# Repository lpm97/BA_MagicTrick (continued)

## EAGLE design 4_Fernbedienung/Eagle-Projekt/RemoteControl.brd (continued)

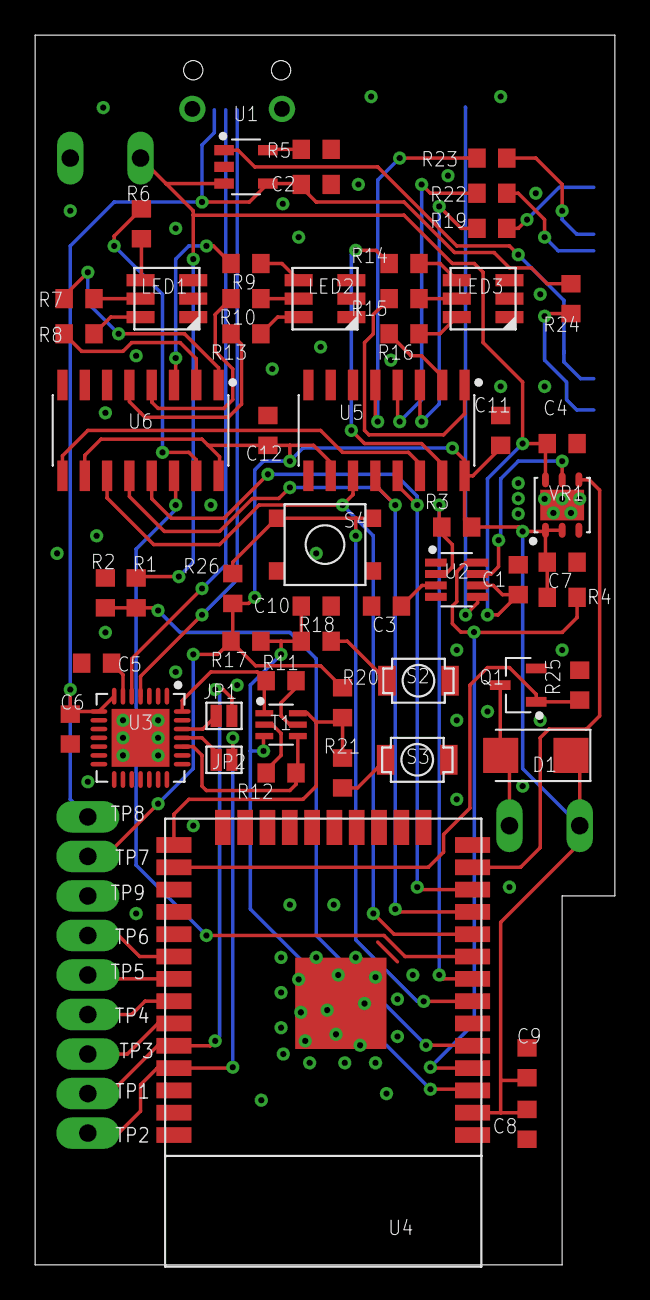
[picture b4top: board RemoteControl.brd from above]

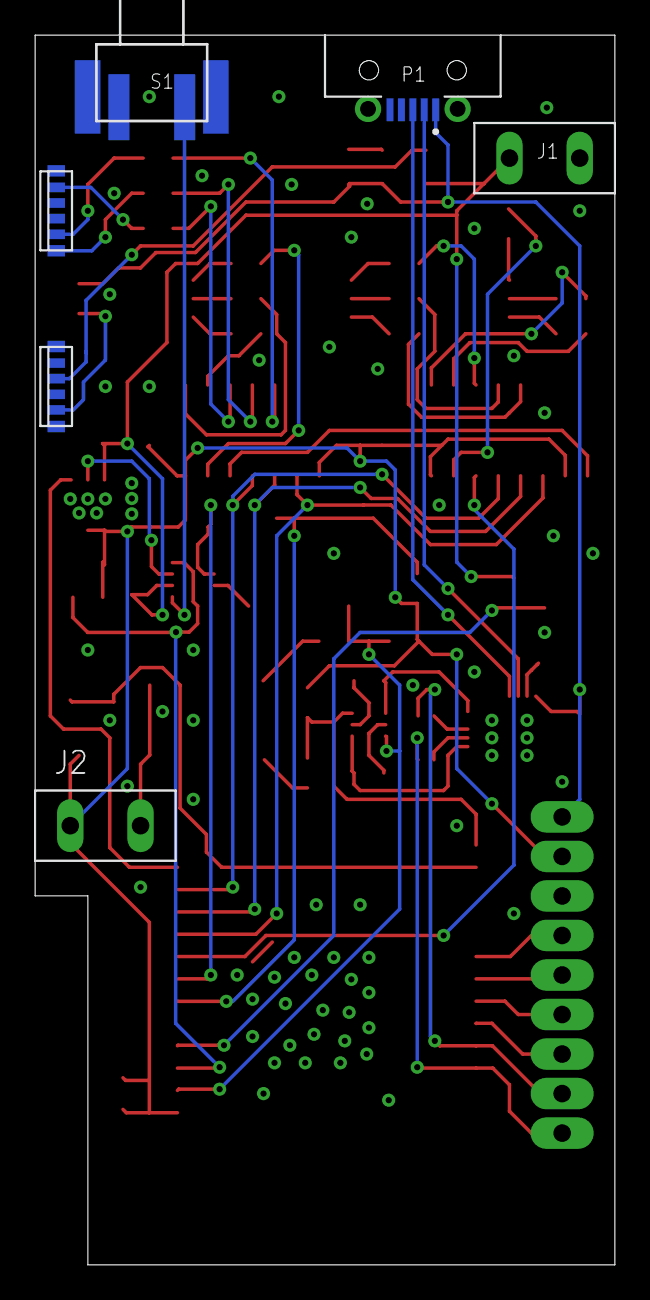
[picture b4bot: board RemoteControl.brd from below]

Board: 2 copper layers, 33.0 x 70.0 mm, 71 parts (6 on the bottom side), 65 nets.

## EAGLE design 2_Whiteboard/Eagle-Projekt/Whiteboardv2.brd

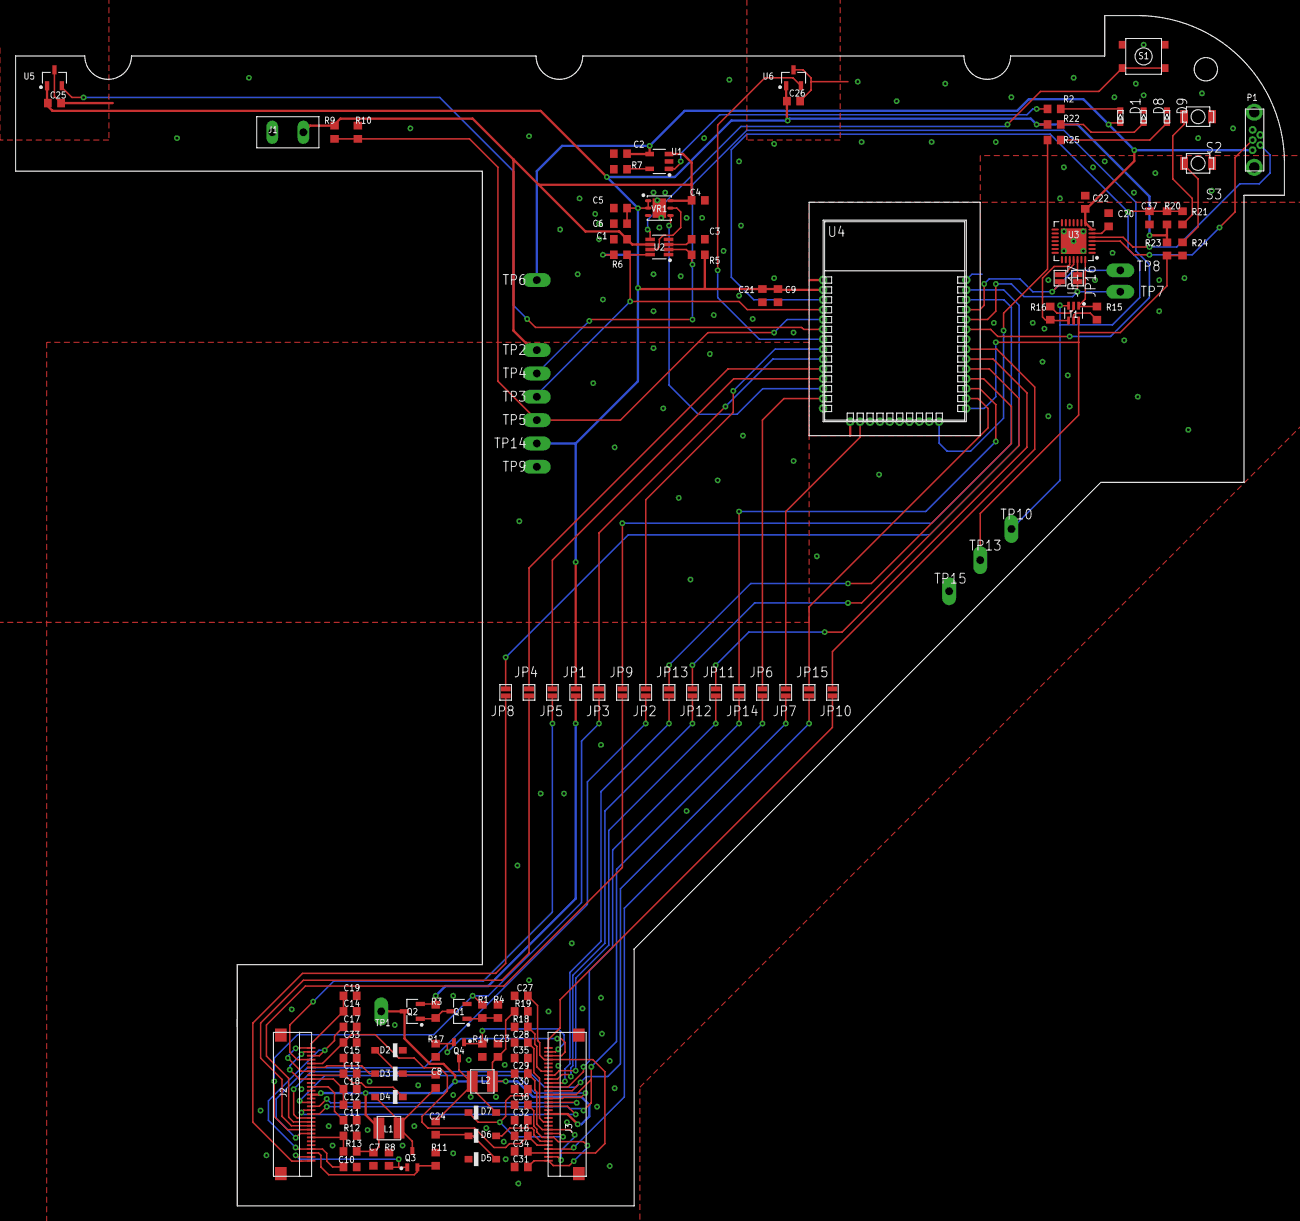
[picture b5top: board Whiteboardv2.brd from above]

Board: 2 copper layers, 163.0 x 152.9 mm, 122 parts (0 on the bottom side), 92 nets.

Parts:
C1, C6, C9: 100nF; 0603
C2, C20: 1uF; 0603
C3, C25, C26: 470nF; 0603
C4, C5, C21, C22, C37: 10uF; 0603
C7, C8, C23, C24: 4.7uF/25V; 0603
C10, C11, C12, C13, C14, C15, C16, C17, C18, C19, C27, C28, C29, C30, C31, C32, C33, C34, C35, C36: 1uF/50V; 0603
D1, D8, D9: 0603_LED
D2, D3, D4, D5, D6, D7: MBR0530; SOD123
J1: CON_2
J2, J3: XF2M-30_CONN; XF2M-30
JP1, JP2, JP3, JP4, JP5, JP6, JP7, JP8, JP9, JP10, JP11, JP12, JP13, JP14, JP15, JP16, JP17: SOLDER_JUMPER
L1, L2: 10uH / 1A; SRN3015_IND
P1: USB_CON_VERTICAL; USB3131
Q1: SS8050-G; SOT23-3
Q2: AO3401A; SOT23-3
Q3, Q4: SI1308EDL; SOT-323
R1: 2.2K; 0603
R2, R22: 1K; 0603
R3, R8, R13, R14, R15, R16, R19, R20, R23: 10K; 0603
R4, R5, R6: 100K; 0603
R7: 1.2K; 0603
R9, R10: 2K; 0603
R11, R17: 1; 0603
R12, R18: 3; 0603
R21, R24, R25: 470; 0603
S1: BUTTON_TL3313AF160QG_2; TL3313AF160QG_2
S2, S3: BUTTON_B3U-1000P; B3U-1000P
T1: MBT3904DW1T1G; SOT23-6
TP1, TP2, TP3, TP4, TP5, TP6, TP7, TP8, TP9, TP10, TP13, TP14, TP15: TP; TEST_PAD
U1: STC4054_BAT_CHARGER; TSOT23-5L
U2: LTC2955-1_ON/OFF_CTLR; SOT23-8
U3: CP2102/9; QFN-28
U4: ESP32-WROOM-32_EMBEDDED
U5, U6: TCS40DPR; SOT23-3
VR1: LD39200PU33R_V-REG; DFN-6

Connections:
3V3_EPD: C7.2, C23.2, J2.P$17, J2.P$18, J3.P$17, J3.P$18, L1.P$1, L2.P$1, Q2.3, R13.2, R19.2, TP1.TP
+3V3: C5.2, C6.2, C9.1, C21.1, C25.1, C26.1, JP1.P$1, R5.1, R6.1, R20.2, R22.2, R23.2, TP14.TP, U4.P$2, U5.1, U6.1, VR1.1, VR1.2
BAT_MONITOR: R9.2, R10.1, TP5.TP, U4.P$5
BUSY_M1: J2.P$8, JP2.P$1
BUSY_M2: J3.P$8, JP11.P$1
BUSY_S1: J2.P$27, JP5.P$1
BUSY_S2: J3.P$27, JP15.P$1
CHRG: R2.1, U1.1
CLK: J2.P$12, J3.P$12, JP7.P$1
CS_M1: J2.P$1, JP8.P$1
CS_M2: J3.P$11, JP14.P$1
CS_S1: J2.P$11, JP9.P$1
CS_S2: J3.P$1, JP10.P$1
DC_1: J2.P$10, JP4.P$1
DC_2: J3.P$10, JP13.P$1
DIN: J2.P$13, J3.P$13, JP6.P$1
DTR: R15.1, T1.1, U3.28
D_N: P1.2, U3.5
D_P: P1.3, U3.4
EN: C37.1, R20.1, R21.2, T1.3, TP10.TP, U4.P$3
GDR1: J2.P$2, Q3.1, R8.2
GDR2: J3.P$2, Q4.1, R14.2
GND: C1.2, C2.2, C3.2, C4.2, C5.1, C6.1, C7.1, C9.2, C10.1, C11.1, C12.1, C13.1, C14.1, C15.1, C16.1, C17.1, C18.1, C19.1, C20.2, C21.2, C22.2, C23.1, C25.2, C26.2, C27.1, C28.1, C29.1, C30.1, C31.1, C32.1, C33.1, C34.1, C35.1, C36.1, C37.2, D2.1, D5.1, D8.K, D9.K, J1.2, J2.P$19, J3.P$19, P1.5, P1.P$6, P1.P$7, Q1.2, R4.1, R7.1, R8.1, R10.2, R11.1, R12.2, R14.1, R17.1, R18.2, S1.1, S1.2, S2.P$1, S3.P$1, TP9.TP, TP15.TP, U1.2, U2.1, U2.4, U3.3, U3.29, U4.P$1, U4.P$15, U4.P$38, U5.3, U6.3, VR1.3, VR1.7
IO0: R23.1, R24.2, T1.6, TP13.TP, U4.P$25
IO2: R25.2, U4.P$24
LSYNC: J2.P$14, J3.P$16
M1M2_SYNC: J2.P$15, J3.P$15
M2M1_SYNC: J2.P$16, J3.P$14
MAG_POS1: U4.P$6, U5.2
MAG_POS2: U4.P$7, U6.2
unnamed: R21.1, S2.P$2
unnamed: JP16.P$1, U3.26
unnamed: R24.1, S3.P$2
unnamed: R15.2, T1.5
unnamed: R16.2, T1.2
unnamed: C20.1, U3.6
unnamed: D8.A, R22.1
unnamed: D1.K, R2.2
unnamed: J3.P$7, R18.1, R19.1
unnamed: C28.2, J3.P$20
unnamed: D9.A, R25.1
unnamed: C8.2, D4.2, L1.P$2, Q3.3
unnamed: J2.P$7, R12.1, R13.1
unnamed: C8.1, D2.2, D3.1
unnamed: C24.2, D7.2, L2.P$2, Q4.3
unnamed: C24.1, D5.2, D6.1
unnamed: Q1.1, R1.2, R4.2
unnamed: Q1.3, Q2.1, R3.2
unnamed: R7.2, U1.5
unnamed: JP4.P$2, U4.P$10
unnamed: C11.2, J2.P$20
unnamed: JP3.P$2, U4.P$9
unnamed: S1.3, S1.4, U2.5
unnamed: JP2.P$2, U4.P$8
unnamed: C3.1, U2.3
unnamed: JP6.P$2, U4.P$13
unnamed: JP8.P$2, U4.P$37
unnamed: JP10.P$2, U4.P$31
unnamed: JP9.P$2, U4.P$36
unnamed: JP5.P$2, U4.P$11
unnamed: JP15.P$2, U4.P$26
unnamed: JP11.P$2, U4.P$30
unnamed: JP12.P$2, U4.P$29
unnamed: JP13.P$2, U4.P$28
unnamed: JP14.P$2, U4.P$27
unnamed: JP7.P$2, U4.P$16
unnamed: JP1.P$2, Q2.2, R3.1
unnamed: JP17.P$1, U3.25
PG: U4.P$12, VR1.4
PWR_EN: U2.7, VR1.5
RESE1: J2.P$3, Q3.2, R11.2
RESE2: J3.P$3, Q4.2, R17.2
RST_1: J2.P$9, JP3.P$1, R1.1
RST_2: J3.P$9, JP12.P$1
RTS: R16.1, T1.4, U3.24
U0RX: JP16.P$2, TP7.TP, U4.P$34
U0TX: JP17.P$2, TP8.TP, U4.P$35
VBAT: C1.1, C4.1, J1.1, R9.1, TP2.TP, U1.3, U2.6, VR1.6
VCOM_M1M2: C16.2, C33.2, J2.P$26, J3.P$26
VGH_M1: C13.2, D4.1, J2.P$23
VGH_M2: C30.2, D7.1, J3.P$23
VGL_M1: C15.2, D3.2, J2.P$25
VGL_M2: C32.2, D6.2, J3.P$25
VSHR_M1S1: C10.2, C17.2, J2.P$4, J2.P$28
VSHR_M2S2: C27.2, C34.2, J3.P$4, J3.P$28
VSH_M1S1: C12.2, C18.2, J2.P$22, J2.P$29
VSH_M2S2: C29.2, C35.2, J3.P$22, J3.P$29
VSL_M1S1: C14.2, C19.2, J2.P$24, J2.P$30
VSL_M2S2: C31.2, C36.2, J3.P$24, J3.P$30
VUSB: C2.1, C22.1, D1.A, P1.1, TP6.TP, U1.4, U3.7, U3.8
~PWR_KILL: R5.2, TP4.TP, U2.2, U4.P$33
~TURN_OFF: R6.2, TP3.TP, U2.8, U4.P$4

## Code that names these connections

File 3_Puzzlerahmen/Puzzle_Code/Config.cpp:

/*****************************************************************************
* | File      	:   Config.cpp
* | Author      :   MM & LM
* | Function    :   GPIO declaration and Module Initialisation        
*----------------
* |	This version:   V1.0
* | Date        :   2021_06_03
/*****************************************************************************/


/* Includes ------------------------------------------------------------------*/
#include "Config.h"

/******************************************************************************
function:  Set GPIO In/Output
******************************************************************************/
void GPIO_Config(void)
{    
    // GPIO
    pinMode(TURN_OFF, INPUT);
    pinMode(BAT_MONITOR, INPUT);
    pinMode(OPEN_PB, INPUT);
    pinMode(TP2, OUTPUT);
    pinMode(DS, OUTPUT);
    pinMode(SHCP, OUTPUT);
    pinMode(STCP, OUTPUT);
    pinMode(OE, OUTPUT);
    pinMode(SLEEP_SOLE, OUTPUT);
    pinMode(IN1_SOLE, OUTPUT);
    pinMode(IN2_SOLE, OUTPUT);
    pinMode(MODE1, OUTPUT);
    pinMode(MODE0, INPUT);
    pinMode(SLEEP_M3, OUTPUT);
    pinMode(DIR_M3, OUTPUT);
    pinMode(STEP_M3, OUTPUT);
    pinMode(SLEEP_M2, OUTPUT);
    pinMode(DIR_M2, OUTPUT);
    pinMode(STEP_M2, OUTPUT);
    pinMode(SLEEP_M1, OUTPUT);
    pinMode(DIR_M1, OUTPUT);
    pinMode(STEP_M1, OUTPUT);
    pinMode(PWR_KILL, OUTPUT);
    
    
    // Init
    digitalWrite(PWR_KILL,  HIGH);
    digitalWrite(MODE1, HIGH);
    digitalWrite(SLEEP_M1, LOW);
    digitalWrite(SLEEP_M2, LOW);
    digitalWrite(SLEEP_M3, LOW);
    digitalWrite(OE, HIGH);
    digitalWrite(IN2_SOLE, LOW);
    digitalWrite(SLEEP_M1, LOW);
    digitalWrite(SLEEP_M2, LOW);
    digitalWrite(SLEEP_M3, LOW);
}


/******************************************************************************
function:	Initialise GPIO and Serial Output
******************************************************************************/
uint8_t moduleInit(void)
{ 
    Debug("ModulInit");
    GPIO_Config();
    return 0;
}


/******************************************************************************
function: Microsecond delay
******************************************************************************/
void Delay_us(uint16_t xus)
{
    uint16_t i;
    while(xus) 
    {
        for(i = 0; i < 30; i++);
        xus--;
    }
}

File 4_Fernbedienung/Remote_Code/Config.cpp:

/*****************************************************************************
* | File      	:   Config.cpp
* | Author      :   MM & LM
* | Function    :   GPIO declaration and Module Initialisation         
*----------------
* |	This version:   V1.0
* | Date        :   2021_06_03
/*****************************************************************************/


/* Includes ------------------------------------------------------------------*/
#include "Config.h"

/******************************************************************************
function:  Set GPIO In/Output
******************************************************************************/
void GPIO_Config(void)
{    
    // GPIO
    pinMode(TURN_OFF, INPUT);
    pinMode(BAT_MONITOR, INPUT);
    pinMode(START_PB, INPUT);
    pinMode(DS, OUTPUT);
    pinMode(OE, OUTPUT);
    pinMode(SHCP, OUTPUT);
    pinMode(STCP, OUTPUT);
    pinMode(PG, INPUT);

    // Attach PWM to VIB MOT
    ledcSetup(0, 5000, 8);
    ledcAttachPin(VIBMOT, 0);

    // Init
    
    digitalWrite(DS,  LOW);
    digitalWrite(OE,  HIGH);
    digitalWrite(SHCP,  LOW);
    digitalWrite(STCP, LOW);
    
    pinMode(PWR_KILL, OUTPUT);
    digitalWrite(PWR_KILL,  HIGH);
    
    ledcWrite(0, 0); // 0-0xFF
}


/******************************************************************************
function:	Initialise GPIO and Serial Output
******************************************************************************/
uint8_t moduleInit(void)
{ 
    Debug("ModulInit");
    GPIO_Config();
    return 0;
}

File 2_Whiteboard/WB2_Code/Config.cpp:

/*****************************************************************************
* | File      	:   Config.cpp
* | Author      :   MM & LM
* | Function    :   GPIO declaration and Module Initialisation   
*----------------
* |	This version:   V1.0
* | Date        :   2021_06_03
/*****************************************************************************/


/* Includes ------------------------------------------------------------------*/
#include "Config.h"

/******************************************************************************
function:  Set GPIO In/Output
******************************************************************************/
void GPIO_Config(void)
{    
    // SPI
    pinMode(SCK_PIN, OUTPUT);
    pinMode(MOSI_PIN, OUTPUT);

    // GPIO
    pinMode(M1_CS_PIN,  OUTPUT);
    pinMode(S1_CS_PIN,  OUTPUT);
    pinMode(M2_CS_PIN,  OUTPUT);
    pinMode(S2_CS_PIN,  OUTPUT);
    pinMode(M1S1_DC_PIN,  OUTPUT);
    pinMode(M2S2_DC_PIN,  OUTPUT);
    pinMode(M1S1_RST_PIN,  OUTPUT);
    pinMode(M2S2_RST_PIN,  OUTPUT);
    pinMode(LED, OUTPUT);
    
    pinMode(M1_BUSY_PIN,  INPUT);
    pinMode(S1_BUSY_PIN,  INPUT);
    pinMode(M2_BUSY_PIN,  INPUT);
    pinMode(S2_BUSY_PIN,  INPUT);
    pinMode(TURN_OFF, INPUT);
    pinMode(PG, INPUT);
    pinMode(BAT_MONITOR, INPUT);
    pinMode(MAG_POS1, INPUT);
    pinMode(MAG_POS2, INPUT);
    
    // Init
    digitalWrite(M1_CS_PIN,  HIGH);
    digitalWrite(S1_CS_PIN,  HIGH);
    digitalWrite(M2_CS_PIN,  HIGH);
    digitalWrite(S2_CS_PIN,  HIGH);
    digitalWrite(SCK_PIN, LOW);

    pinMode(PWR_KILL, OUTPUT);
    digitalWrite(PWR_KILL,  HIGH);
}


/******************************************************************************
function:	Initialise GPIO and Serial Output
******************************************************************************/
uint8_t moduleInit(void)
{ 
    Debug("ModulInit");
    GPIO_Config();
    return 0;
}



/******************************************************************************
function: Microsecond delay
******************************************************************************/
void Delay_us(uint16_t xus)
{
    uint16_t i;
    while(xus) 
    {
        for(i = 0; i < 30; i++);
        xus--;
    }
}

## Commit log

2021-06-11 Project Upload
